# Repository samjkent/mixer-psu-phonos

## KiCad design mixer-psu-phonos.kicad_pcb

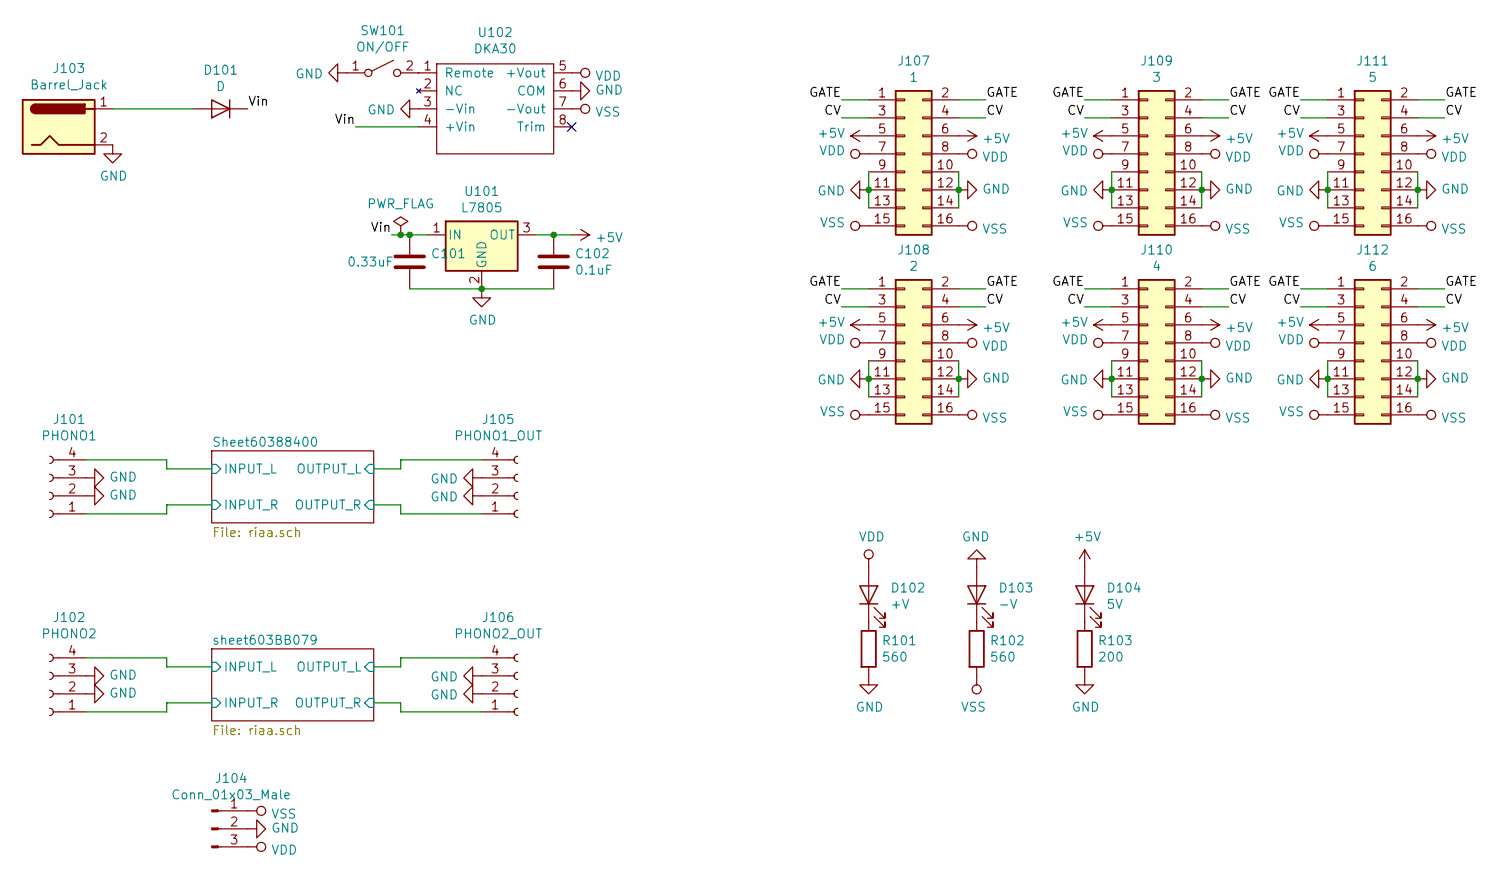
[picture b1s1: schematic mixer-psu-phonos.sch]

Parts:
C101: 0.33uF; C_0805_2012Metric
C102: 0.1uF; C_0805_2012Metric
D101: D; D_SOD-123F
D102: +V; LED_0805_2012Metric
D103: -V; LED_0805_2012Metric
D104: 5V; LED_0805_2012Metric
J101: PHONO1; PinHeader_1x04_P2.54mm_Vertical
J102: PHONO2; PinHeader_1x04_P2.54mm_Vertical
J103: Barrel_Jack; PinHeader_1x02_P2.54mm_Vertical
J104: Conn_01x03_Male; PinSocket_1x03_P2.54mm_Vertical
J105: PHONO1_OUT; PinHeader_1x04_P2.54mm_Vertical
J106: PHONO2_OUT; PinHeader_1x04_P2.54mm_Vertical
J107: 1; PinHeader_2x08_P2.54mm_Vertical
J108: 2; PinHeader_2x08_P2.54mm_Vertical
J109: 3; PinHeader_2x08_P2.54mm_Vertical
J110: 4; PinHeader_2x08_P2.54mm_Vertical
J111: 5; PinHeader_2x08_P2.54mm_Vertical
J112: 6; PinHeader_2x08_P2.54mm_Vertical
R101, R102: 560; R_0402_1005Metric
R103: 200; R_0402_1005Metric
SW101: ON/OFF; PinSocket_1x02_P2.54mm_Vertical
U101: L7805; TO-252-2
U102: DKA30

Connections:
+5V: C102.1, D104.2 (A), J107.5, J107.6, J108.5, J108.6, J109.5, J109.6, J110.5, J110.6, J111.5, J111.6, J112.5, J112.6, U101.3 (OUT)
/CV: J107.3, J107.4, J108.3, J108.4, J109.3, J109.4, J110.3, J110.4, J111.3, J111.4, J112.3, J112.4
/GATE: J107.1, J107.2, J108.1, J108.2, J109.1, J109.2, J110.1, J110.2, J111.1, J111.2, J112.1, J112.2
/Sheet60388400/INPUT_L: J101.4; also elsewhere on the board
/Sheet60388400/INPUT_R: J101.1; also elsewhere on the board
/Sheet60388400/OUTPUT_L: J105.4; also elsewhere on the board
/Sheet60388400/OUTPUT_R: J105.1; also elsewhere on the board
/Vin: C101.1, D101.1 (K), U101.1 (IN), U102.4 (+Vin)
/sheet603BB079/INPUT_L: J102.4; also elsewhere on the board
/sheet603BB079/INPUT_R: J102.1; also elsewhere on the board
/sheet603BB079/OUTPUT_L: J106.4; also elsewhere on the board
/sheet603BB079/OUTPUT_R: J106.1; also elsewhere on the board
GND: C101.2, C102.2, D103.2 (A), J101.2, J101.3, J102.2, J102.3, J103.2, J104.2, J105.2, J105.3, J106.2, J106.3, J107.9, J107.10, J107.11, J107.12, J107.13, J107.14, J108.9, J108.10, J108.11, J108.12, J108.13, J108.14, J109.9, J109.10, J109.11, J109.12, J109.13, J109.14, J110.9, J110.10, J110.11, J110.12, J110.13, J110.14, J111.9, J111.10, J111.11, J111.12, J111.13, J111.14, J112.9, J112.10, J112.11, J112.12, J112.13, J112.14, R101.2, R103.2, SW101.1 (A), U101.2 (GND), U102.3 (-Vin), U102.6 (COM); also elsewhere on the board
unnamed: D101.2 (A), J103.1
unnamed: D102.1 (K), R101.1
unnamed: D103.1 (K), R102.1
unnamed: D104.1 (K), R103.1
unnamed: SW101.2 (B), U102.1 (Remote)
VDD: D102.2 (A), J104.3, J107.7, J107.8, J108.7, J108.8, J109.7, J109.8, J110.7, J110.8, J111.7, J111.8, J112.7, J112.8, U102.5 (+Vout); also elsewhere on the board
VSS: J104.1, J107.15, J107.16, J108.15, J108.16, J109.15, J109.16, J110.15, J110.16, J111.15, J111.16, J112.15, J112.16, R102.2, U102.7 (-Vout); also elsewhere on the board

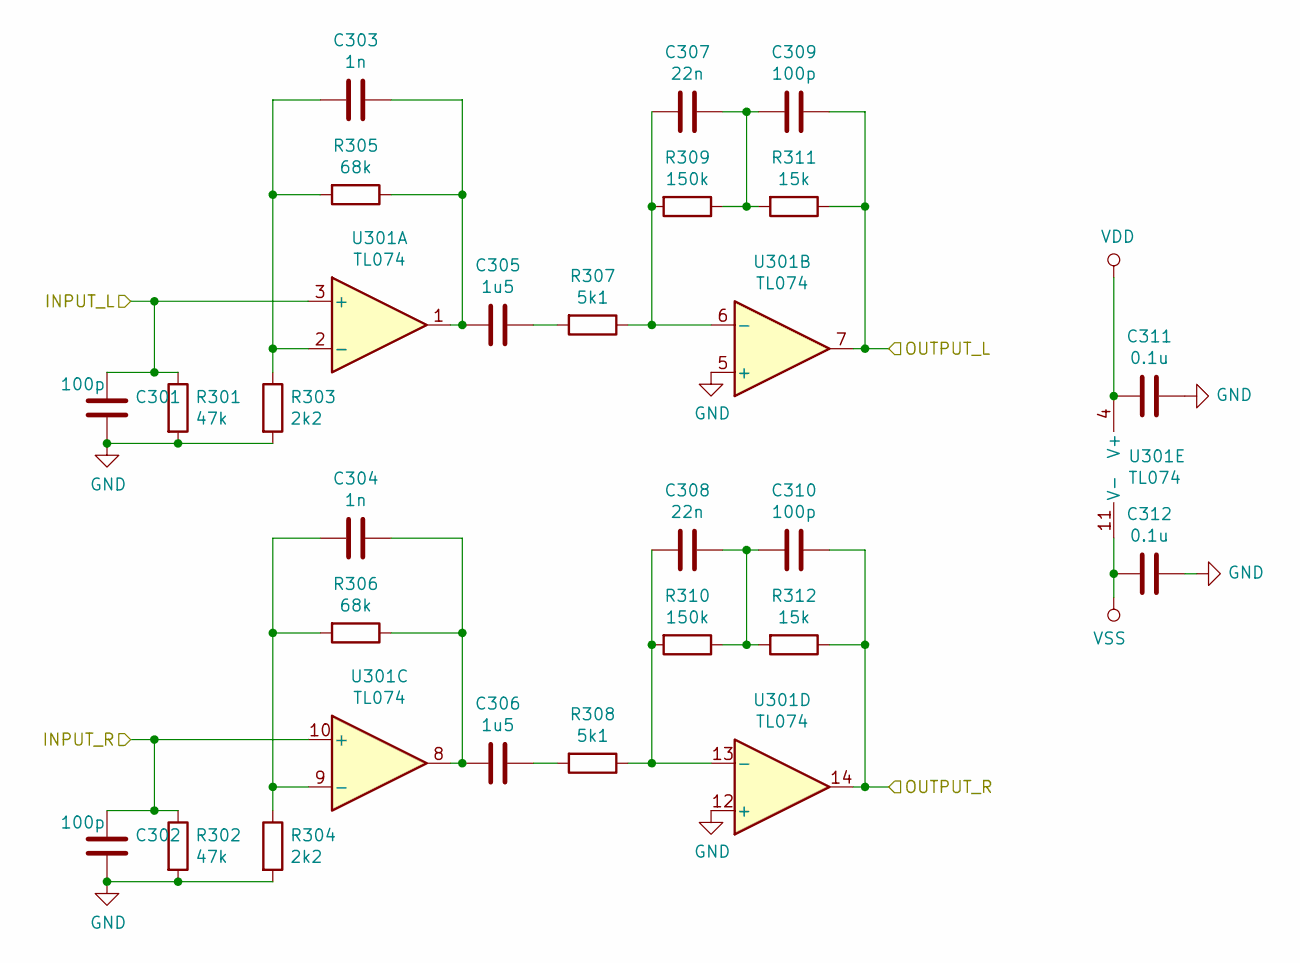
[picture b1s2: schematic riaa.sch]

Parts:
C201, C202, C209, C210: 100p; C_0402_1005Metric
C203, C204: 1n; C_0402_1005Metric
C205, C206: 1u5; C_1206_3216Metric
C207, C208: 22n; C_0402_1005Metric
C211, C212: 0.1u; C_0402_1005Metric
R201, R202: 47k; R_0402_1005Metric
R203, R204: 2k2; R_0402_1005Metric
R205, R206: 68k; R_0402_1005Metric
R207, R208: 5k1; R_0402_1005Metric
R209, R210: 150k; R_0402_1005Metric
R211, R212: 15k; R_0402_1005Metric
U201: TL074; SOIC-14_3.9x8.7mm_P1.27mm

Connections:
/Sheet60388400/INPUT_L: C201.1, R201.1, U201.3 (+); also elsewhere on the board
/Sheet60388400/INPUT_R: C202.1, R202.1, U201.10 (+); also elsewhere on the board
/Sheet60388400/OUTPUT_L: C209.2, R211.1, U201.7; also elsewhere on the board
/Sheet60388400/OUTPUT_R: C210.2, R212.1, U201.14; also elsewhere on the board
GND: C201.2, C202.2, C211.1, C212.1, R201.2, R202.2, R203.2, R204.2, U201.5 (+), U201.12 (+); also elsewhere on the board
unnamed: C203.1, C205.2, R205.1, U201.1
unnamed: C203.2, R203.1, R205.2, U201.2 (-)
unnamed: C204.1, C206.2, R206.1, U201.8
unnamed: C204.2, R204.1, R206.2, U201.9 (-)
unnamed: C205.1, R207.2
unnamed: C206.1, R208.2
unnamed: C207.1, C209.1, R209.1, R211.2
unnamed: C207.2, R207.1, R209.2, U201.6 (-)
unnamed: C208.1, C210.1, R210.1, R212.2
unnamed: C208.2, R208.1, R210.2, U201.13 (-)
VDD: C211.2, U201.4 (V+); also elsewhere on the board
VSS: C212.2, U201.11 (V-); also elsewhere on the board

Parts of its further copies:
C301, C302, C309, C310: 100p; C_0402_1005Metric
C303, C304: 1n; C_0402_1005Metric
C305, C306: 1u5; C_1206_3216Metric
C307, C308: 22n; C_0402_1005Metric
C311, C312: 0.1u; C_0402_1005Metric
R301, R302: 47k; R_0402_1005Metric
R303, R304: 2k2; R_0402_1005Metric
R305, R306: 68k; R_0402_1005Metric
R307, R308: 5k1; R_0402_1005Metric
R309, R310: 150k; R_0402_1005Metric
R311, R312: 15k; R_0402_1005Metric
U301: TL074; SOIC-14_3.9x8.7mm_P1.27mm

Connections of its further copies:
/sheet603BB079/INPUT_L: C301.1, R301.1, U301.3 (+); also elsewhere on the board
/sheet603BB079/INPUT_R: C302.1, R302.1, U301.10 (+); also elsewhere on the board
/sheet603BB079/OUTPUT_L: C309.2, R311.1, U301.7; also elsewhere on the board
/sheet603BB079/OUTPUT_R: C310.2, R312.1, U301.14; also elsewhere on the board
GND: C301.2, C302.2, C311.1, C312.1, R301.2, R302.2, R303.2, R304.2, U301.5 (+), U301.12 (+); also elsewhere on the board
unnamed: C303.1, C305.2, R305.1, U301.1
unnamed: C303.2, R303.1, R305.2, U301.2 (-)
unnamed: C304.1, C306.2, R306.1, U301.8
unnamed: C304.2, R304.1, R306.2, U301.9 (-)
unnamed: C305.1, R307.2
unnamed: C306.1, R308.2
unnamed: C307.1, C309.1, R309.1, R311.2
unnamed: C307.2, R307.1, R309.2, U301.6 (-)
unnamed: C308.1, C310.1, R310.1, R312.2
unnamed: C308.2, R308.1, R310.2, U301.13 (-)
VDD: C311.2, U301.4 (V+); also elsewhere on the board
VSS: C312.2, U301.11 (V-); also elsewhere on the board

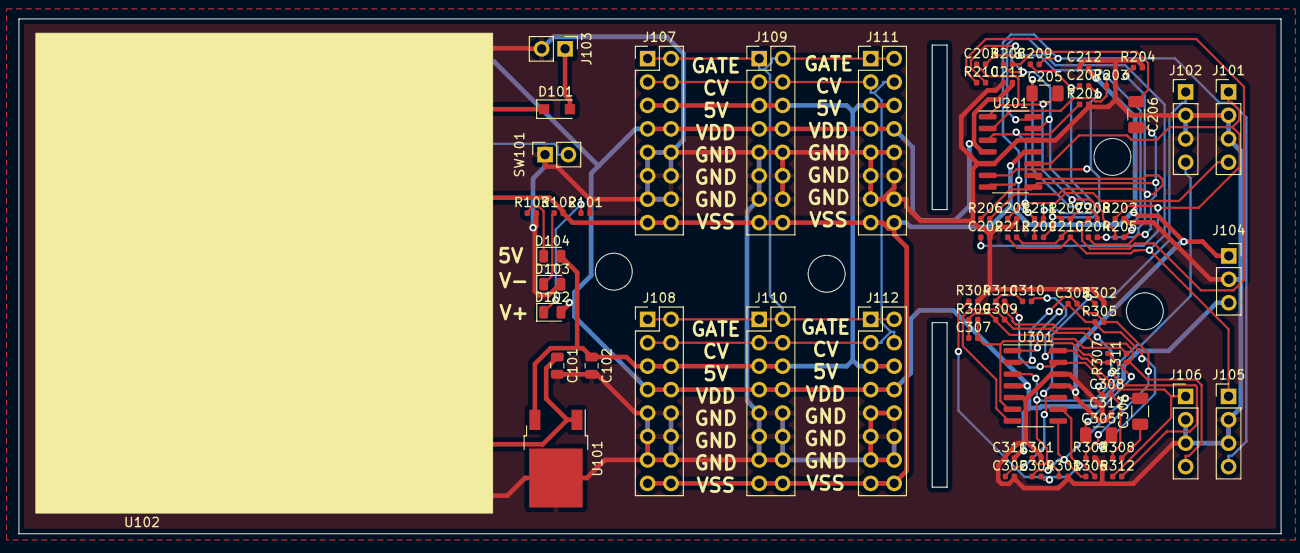
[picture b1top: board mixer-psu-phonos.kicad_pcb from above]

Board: 2 copper layers, 136.8 x 55.8 mm, 74 parts (0 on the bottom side), 40 nets.
